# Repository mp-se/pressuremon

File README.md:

# Pressure Monitor for Beer Brewing

PressureMon is a device for measuring pressure in storage or during fermentation.  

It supports ESP32s2 mini, ESP32s3 mini, ESP32c3 mini, ESP32c3 pico and pico and I2C compatible pressure sensors, currently the brand XIDIBEI is supported which has a good range of encapsulated sensors.

Flashing can be done using https://www.gravitymon.com/flasher/index.html which also will help with wifi setup.

Documentation and flashing instructions are available on the [GravityMon PressureMon project page](https://gravitymon.com/project-pressuremon.html)

PCB design is located [here](https://github.com/mp-se/pcb-designs/) 

3D models for a case can be found in the 3d directory on github.

If you want to support my work you can do that through these options

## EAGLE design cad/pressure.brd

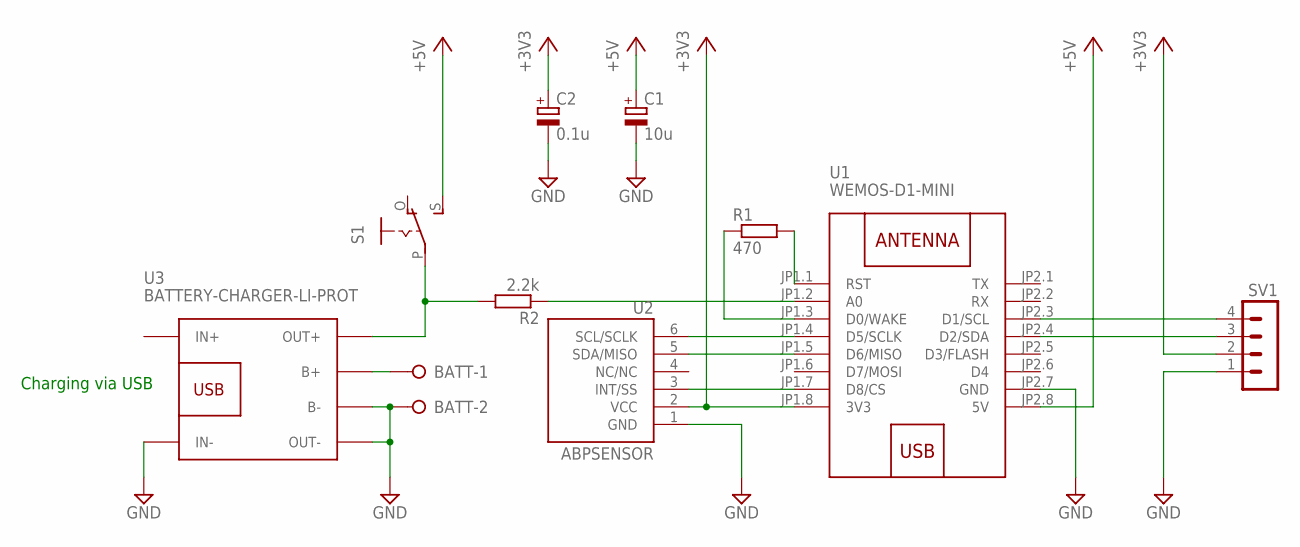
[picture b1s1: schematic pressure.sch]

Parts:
BATT: W237-02P; W237-132
C1: 10u; E2,5-5
C2: 0.1u; E2,5-5
R1: 470; 0207/10
R2: 2.2k; 0207/10
S1: EG1218S; EG1218
SV1: 4-DIGIT-LED; MA04-1
U1: WEMOS-D1-MINI
U2: ABPSENSOR; ABP-DIP6
U3: BATTERY-CHARGER-LI-PROT

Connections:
+3V3: C2.+, SV1.2, U1.JP1.8 (3V3), U2.2 (VCC)
+5V: C1.+, S1.S, U1.JP2.8 (5V)
GND: BATT.2, C1.-, C2.-, SV1.1, U1.JP2.7 (GND), U2.1 (GND), U3.B-, U3.IN-, U3.OUT-
unnamed: U1.JP1.5 (D6/MISO), U2.5 (SDA/MISO)
unnamed: U1.JP1.4 (D5/SCLK), U2.6 (SCL/SCLK)
unnamed: SV1.3, U1.JP2.4 (D2/SDA)
unnamed: U1.JP1.7 (D8/CS), U2.3 (INT/SS)
unnamed: SV1.4, U1.JP2.3 (D1/SCL)
unnamed: R1.1, U1.JP1.3 (D0/WAKE)
unnamed: R1.2, U1.JP1.1 (RST)
unnamed: BATT.1, U3.B+
unnamed: R2.1, U1.JP1.2 (A0)
unnamed: R2.2, S1.P, U3.OUT+

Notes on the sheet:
Charging via USB

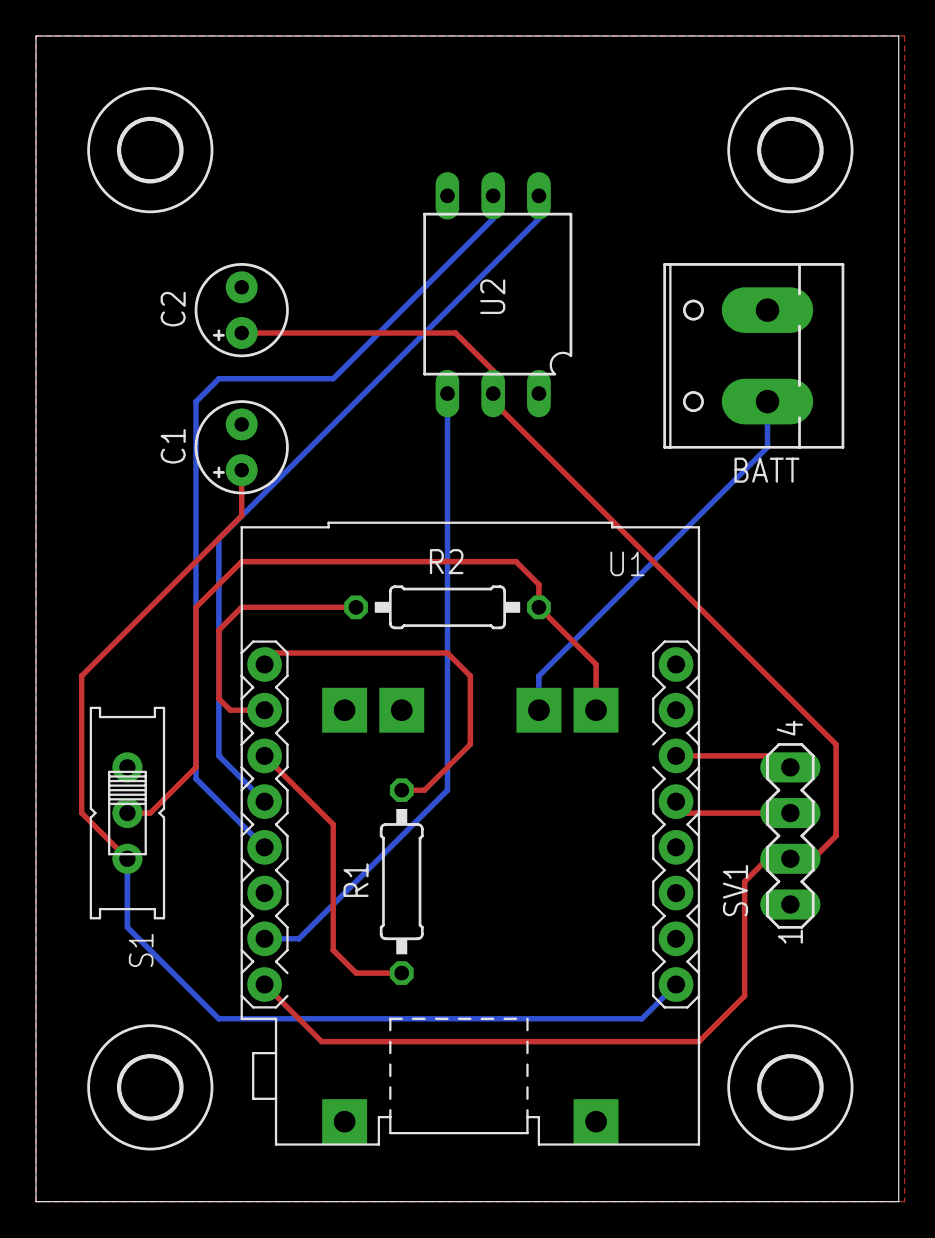
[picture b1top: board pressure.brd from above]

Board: 2 copper layers, 47.9 x 64.8 mm, 14 parts (1 on the bottom side), 13 nets.

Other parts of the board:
U$1, U$2, U$3, U$4: 3,3

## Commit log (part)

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2021-02-23 Initial version, not fully tested
2021-02-24 Added testcases for api
2021-02-25 Added id checks for reset/wifi
2021-02-25 Created pcb
2021-02-25 new version baseline 0.2
2021-02-25 Version file
2021-02-28 Change sleep mode + added web debug option
2021-03-11 Added pressure sensor settings to status
2021-03-11 Moved pressure sensor status to debug
2021-03-11 Added headers to post requests, fixed BF
2021-03-12 Build 0.2.1
2021-03-28 Removed LED
2021-03-28 Copy files to /bin after build
2021-03-28 Updated config för DRD
2021-03-29 Added UI and refactor API's
2021-03-29 fixed 2 bugs
2021-03-30 New test build
2021-03-30 Deleted file
2021-04-01 Swapped wifimanager and tested drd
2023-11-05 Refactor for espframework and esp32
2023-11-05 Fix UI errors
2024-08-12 Update build deps
2024-08-12 Remove 32 binaries
2024-08-12 Remove old html files
2024-08-12 Add build scripts
2024-08-12 Refactor code to match new espframework
2024-08-12 Added example ui files
2024-08-12 Remove old test files
2024-08-12 Add s2 binaries
2024-08-13 Update pressure unit tags
2024-08-13 Upd gitignore
2024-08-14 Update version
2024-08-14 Update licence
2024-08-14 Refactor code to match esp fwk 1.0
2024-08-14 Update sensor defintions
2024-08-14 Updates connected to presssure sensors
2024-08-14 Added dependant as lib
2024-08-14 Added UI build
2024-08-14 Change pressure key
2024-08-14 Fixed temp in status
2024-08-14 Add build
2024-08-14 Fixed formatting for data
2024-08-14 GitHub Action Build
2024-10-14 Refactor and add support for new pressure sensor
2024-10-15 Fix status flag
2024-10-15 Migrate to espfwk 1.1
2025-01-10 Refactor code, add xidibei sensor support, prepare for merge with gravitymon project for one common codebase
2025-01-10 Adding i2c scanner
2025-01-10 Remove build workflow
2025-01-10 Adding datascheets for XDB401
2025-01-11 Adding multiplexer support
2025-01-12 Update schmatic and moved specification to own folder
2025-01-12 Tested sensor drivers and added optional schematics
2025-01-13 Cleanup and focus on xidibei sensors for first release
2025-01-22 Adding analog sensor support via external ADC
2025-01-22 Remove unused code
2025-01-23 Adding voltage method for sensor classes
2025-01-25 Adding new target and 0.2hpa sensor
2025-01-26 Update code to work with i2c sensor
2025-01-27 Remove unused script
2025-01-28 Update code to align with gravitymon implementation
2025-01-29 Align with gravitymon
2025-01-29 Adding validation of min/max pressure
2025-01-29 Update logging levels, fixed conversion of negative pressure
2025-01-30 update code
2025-01-30 Update action
2025-01-30 Update build
2025-01-30 Adding bins
2025-01-30 Adding readme
2025-01-30 Added flash bin for s3
2025-01-30 Adding flash script
2025-01-30 Update html
2025-01-30 Limit validation to max pressure
2025-01-31 Update workflow
2025-01-31 Force build
2025-01-31 Adding additional targets
2025-01-31 Adding more targets
2025-01-31 Adding flash files for c3 and s2
2025-02-06 Update build scripts
2025-02-14 Update build process
2025-03-12 Adding 2 pcb options
2025-03-28 Update build script
2025-03-29 Update pcb for digital sensors
2025-03-29 Update pcb
2025-04-07 Refactor and move function to pressure files
2025-04-07 Initial commit on orphan branch
2025-04-08 Adding documentation
2025-04-09 Update dependency
2025-04-09 Update documentation
2025-04-14 Sync with gravmon repo
2025-04-14 Adding new partition file
2025-04-14 Update partition setup
2025-04-20 Updating schematic, adding off switch
2025-04-20 Updating docs
2025-04-20 Adding off switch
2025-04-25 Update build instructions for the hardware
2025-04-27 Adding mounting holes to pcb
2025-04-27 Update analog pcb
2025-05-07 Update readme and move schema
2025-05-11 Move code from gravitymon project
2025-05-11 Update dependecies + precommit
2025-05-15 Fix issue with tempsensor crashing
2025-05-16 Using battery percentage with battery type
2025-05-23 Fixed force config feature
2025-05-23 Update to release
2025-05-24 Adding define to enable second sensor
2025-05-24 Adding driver for OLED display
2025-05-25 Added message when display not found
2025-05-25 Bump version, enable sensor 2
2025-05-25 Update display output
2025-05-25 Adding support for custom analog sensors
2025-05-25 Update flasher link
2025-05-25 Switch to kpa for custom analog
2025-05-26 Enable i2c scanning of second bus
2025-05-28 Fix link to flasher
2025-05-28 Update code for second i2c bus.
2025-05-29 Adding SoftWire for second i2c bus on boards with one hardware controller
2025-06-08 Remove debug prints
2025-06-08 FIxed temperature on display
2025-06-08 Update docs
2025-06-09 Build beta 1
2025-06-15 Fixed LED on pico board
2025-06-15 Update push test api
2025-06-15 Bump version
2025-06-25 Update dependencies
2025-08-05 Update deps and increase stack for webserver
2025-09-09 Rename bin and add feature api
2025-09-09 Update deps
2025-09-10 Update bin names
2025-09-27 Adding support for Arduino 3.x
2025-09-27 Downgrade to 6.11
2025-09-27 Remove 8266 deps
2025-10-01 Optimzie build and fix potential issues
2025-10-03 Fiorce build
2025-10-12 Adding script to copy ui files
2025-10-18 Fix deps
2025-10-18 Fix battery reading setup
2025-12-25 Adding temp value to loop serial output
2025-12-28 Revered to arduino 2.x for smaller size
2025-12-28 Update fileviewer
2025-12-28 Added 3d model
2025-12-28 Update release notes
2026-04-09 Switch to dual license

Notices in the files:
parts and their libraries:
diy-modules: Released under the Creative Commons Attribution 4.0 International License: http://creativecommons.org/licenses/by/4.0
